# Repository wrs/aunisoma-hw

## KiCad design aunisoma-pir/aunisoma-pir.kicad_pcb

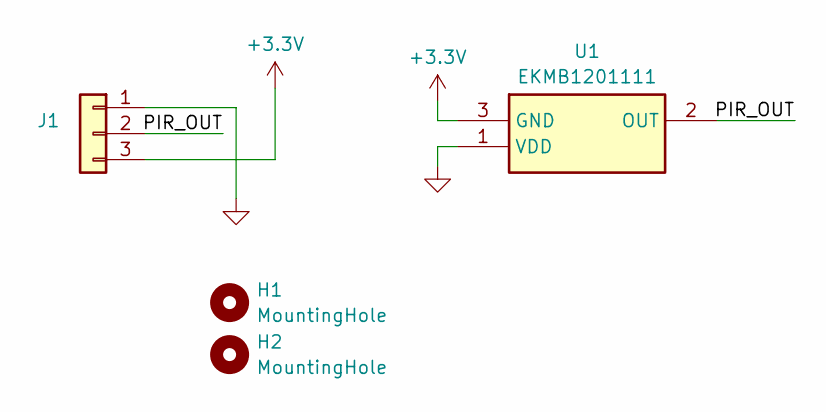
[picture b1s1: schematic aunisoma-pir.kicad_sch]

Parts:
H1, H2: MountingHole; MountingHole_3.2mm_M3
J1: PIR1; JST_PH_B3B-PH-K_1x03_P2.00mm_Vertical
U1: EKMB1201111; Mouser Part Number 769-EKMB1201111

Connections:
+3.3V: J1.3, U1.3 (GND)
/PIR_OUT: J1.2, U1.2 (OUT)
GND: J1.1, U1.1 (VDD)

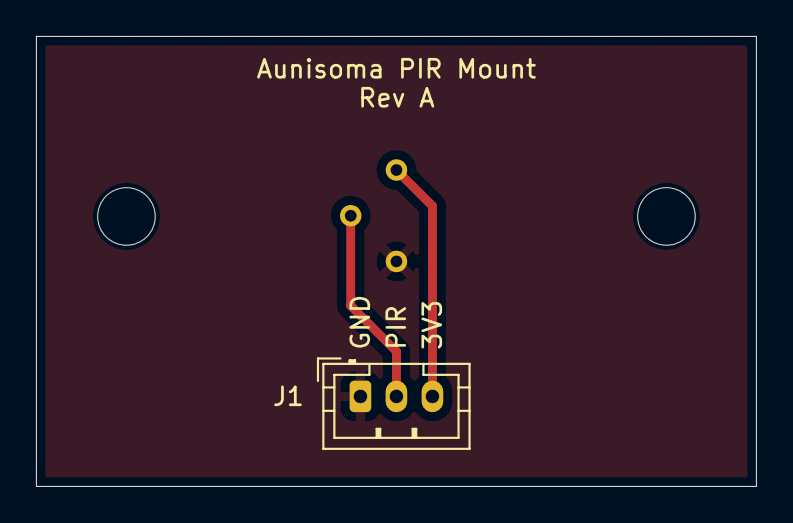
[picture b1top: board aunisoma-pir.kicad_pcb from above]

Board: 2 copper layers, 40.0 x 25.0 mm, 4 parts (1 on the bottom side), 3 nets.

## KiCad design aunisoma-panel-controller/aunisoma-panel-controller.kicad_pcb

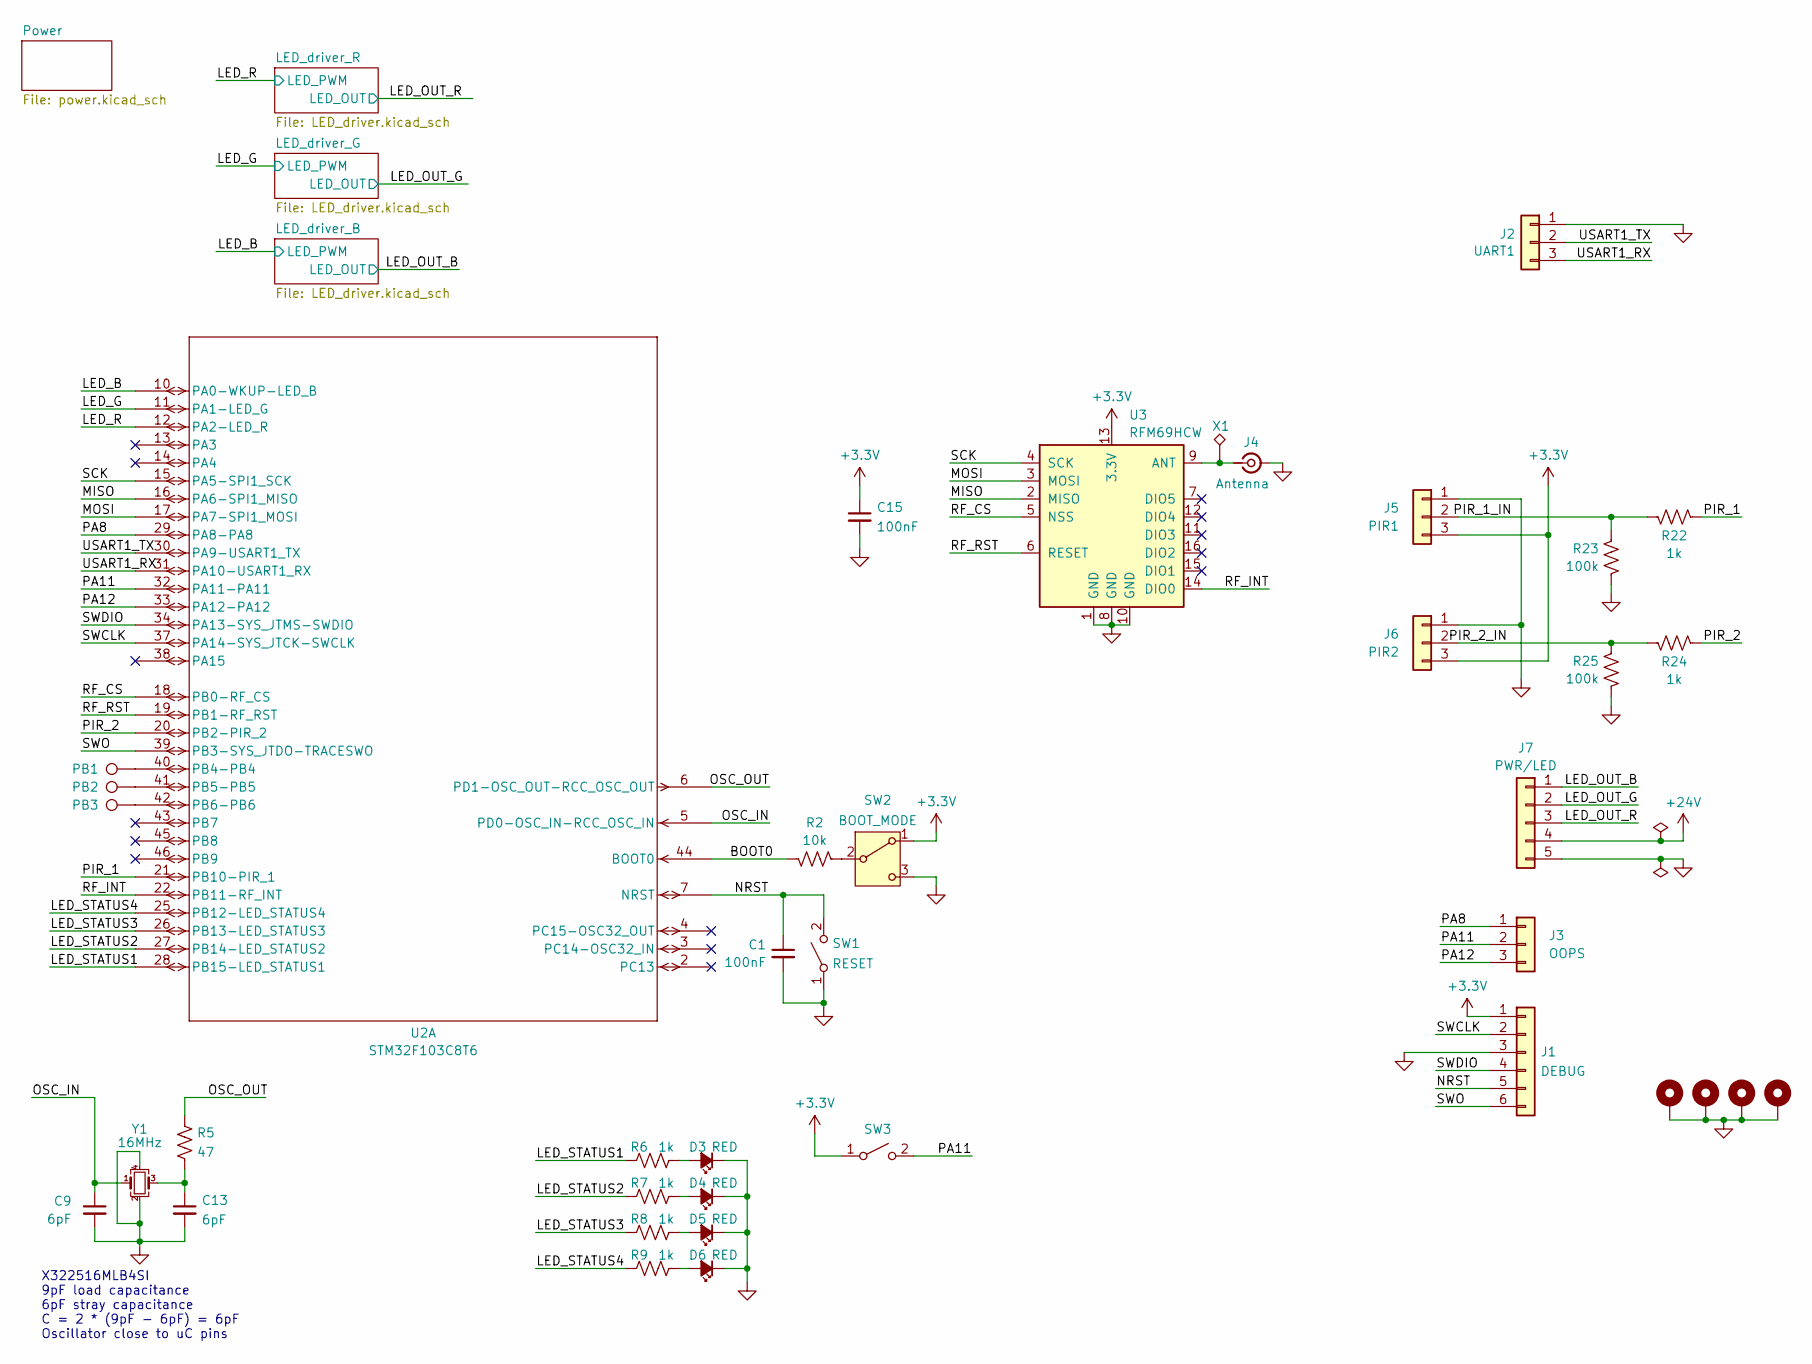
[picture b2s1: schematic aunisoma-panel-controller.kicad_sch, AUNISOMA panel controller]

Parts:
C1, C15: 100nF; C_0402_1005Metric; LCSC C1525
C9, C13: 6pF; C_0603_1608Metric; LCSC C37474
D3, D4, D5, D6: RED; LED_0805_2012Metric; LCSC C84256
H1, H2, H3, H4: MountingHole_Pad; MountingHole_3.2mm_M3_Pad_Via
J1: DEBUG; PinHeader_1x06_P2.54mm_Vertical
J2: UART1; PinHeader_1x03_P2.54mm_Vertical
J3: OOPS; PinHeader_1x03_P2.54mm_Vertical
J4: Conn_Coaxial_Small; IPEX-SMD_KMC1001-F007-7F; LCSC C426219
J5: PIR1; JST_PH_B3B-PH-K_1x03_P2.00mm_Vertical
J6: PIR2; JST_PH_B3B-PH-K_1x03_P2.00mm_Vertical
J7: PWR/LED; JST_PH_B5B-PH-K_1x05_P2.00mm_Vertical; LCSC C158028
PB1, PB2, PB3: TestPoint; TestPoint_Pad_1.0x1.0mm
R2: 10k; R_0603_1608Metric; LCSC C25804
R5: 47; R_0603_1608Metric; LCSC C23182
R6, R7, R8, R9: 1k; R_0603_1608Metric; LCSC C8218
R22, R24: 1k; R_0603_1608Metric; LCSC C25803
R23, R25: 100k; R_0603_1608Metric; LCSC C25803
SW1, SW3: SW-SMD_4P-L5.1-W5.1-P3.70-LS6.5-TL-2
SW2: SW_SPDT_PCM12; LCSC C109335
U2: STM32F103C8T6; LQFP-48_7x7mm_P0.5mm; LCSC C8734
U3: RFM69HCW; HOPERF_RFM69HW_SMD_TH
X1: Antenna; TestPoint_THTPad_D2.0mm_Drill1.0mm
Y1: 16MHz; Crystal_SMD_3225-4Pin_3.2x2.5mm; LCSC C13738

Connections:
+3.3V: C15.1, J1.1, J5.3, J6.3, SW2.1 (A), SW3.1 (A), U3.13 (3.3V); also elsewhere on the board
+24V: J7.4; also elsewhere on the board
/BOOT0: R2.2, U2.44 (BOOT0)
/LED_B: U2.10 (PA0-WKUP-LED_B); also elsewhere on the board
/LED_G: U2.11 (PA1-LED_G); also elsewhere on the board
/LED_OUT_B: J7.1; also elsewhere on the board
/LED_OUT_G: J7.2; also elsewhere on the board
/LED_OUT_R: J7.3; also elsewhere on the board
/LED_R: U2.12 (PA2-LED_R); also elsewhere on the board
/LED_STATUS1: R6.2, U2.28 (PB15-LED_STATUS1)
/LED_STATUS2: R7.2, U2.27 (PB14-LED_STATUS2)
/LED_STATUS3: R8.2, U2.26 (PB13-LED_STATUS3)
/LED_STATUS4: R9.2, U2.25 (PB12-LED_STATUS4)
/MISO: U2.16 (PA6-SPI1_MISO), U3.2 (MISO)
/MOSI: U2.17 (PA7-SPI1_MOSI), U3.3 (MOSI)
/NRST: C1.1, J1.5, SW1.2 (B), U2.7 (NRST)
/OSC_IN: C9.1, U2.5 (PD0-OSC_IN-RCC_OSC_IN), Y1.1
/OSC_OUT: R5.2, U2.6 (PD1-OSC_OUT-RCC_OSC_OUT)
/PA8: J3.1, U2.29 (PA8-PA8)
/PA11: J3.2, SW3.2 (B), U2.32 (PA11-PA11)
/PA12: J3.3, U2.33 (PA12-PA12)
/PIR_1: R22.1, U2.21 (PB10-PIR_1)
/PIR_1_IN: J5.2, R22.2, R23.2
/PIR_2: R24.1, U2.20 (PB2-PIR_2)
/PIR_2_IN: J6.2, R24.2, R25.2
/RF_CS: U2.18 (PB0-RF_CS), U3.5 (NSS)
/RF_INT: U2.22 (PB11-RF_INT), U3.14 (DIO0)
/RF_RST: U2.19 (PB1-RF_RST), U3.6 (RESET)
/SCK: U2.15 (PA5-SPI1_SCK), U3.4 (SCK)
/SWCLK: J1.2, U2.37 (PA14-SYS_JTCK-SWCLK)
/SWDIO: J1.4, U2.34 (PA13-SYS_JTMS-SWDIO)
/SWO: J1.6, U2.39 (PB3-SYS_JTDO-TRACESWO)
/USART1_RX: J2.3, U2.31 (PA10-USART1_RX)
/USART1_TX: J2.2, U2.30 (PA9-USART1_TX)
GND: C1.2, C9.2, C13.2, C15.2, D3.1 (K), D4.1 (K), D5.1 (K), D6.1 (K), H1.1, H2.1, H3.1, H4.1, J1.3, J2.1, J4.2 (Ext), J5.1, J6.1, J7.5, R23.1, R25.1, SW1.1 (A), SW2.3 (C), U3.1 (GND), U3.8 (GND), U3.10 (GND), Y1.2, Y1.4; also elsewhere on the board
unnamed: C13.1, R5.1, Y1.3
unnamed: D3.2 (A), R6.1
unnamed: D4.2 (A), R7.1
unnamed: D5.2 (A), R8.1
unnamed: D6.2 (A), R9.1
unnamed: J4.1 (In), U3.9 (ANT), X1.1
unnamed: R2.1, SW2.2 (B)
unnamed: PB1.1, U2.40 (PB4-PB4)
unnamed: PB2.1, U2.41 (PB5-PB5)
unnamed: PB3.1, U2.42 (PB6-PB6)

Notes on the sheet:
X322516MLB4SI 9pF load capacitance 6pF stray capacitance C = 2 * (9pF - 6pF) = 6pF Oscillator close to uC pins

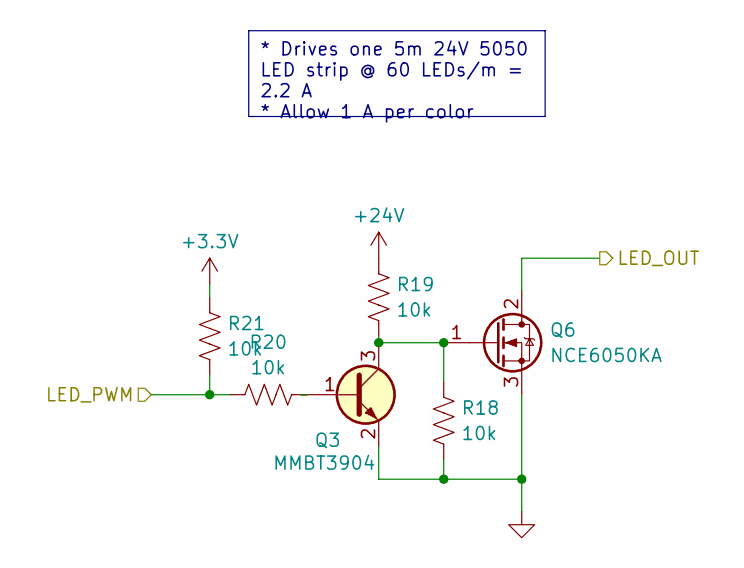
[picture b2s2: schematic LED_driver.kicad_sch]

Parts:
Q3: MMBT3904; SOT-23; LCSC C20526
Q6: NCE6050KA; TO-252-2; LCSC C620154
R18, R19, R20, R21: 10k; R_0603_1608Metric; LCSC C25803

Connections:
+3.3V: R21.2; also elsewhere on the board
+24V: R19.2; also elsewhere on the board
/LED_OUT_R: Q6.2 (D); also elsewhere on the board
/LED_R: R20.2, R21.1; also elsewhere on the board
GND: Q3.2 (E), Q6.3 (S), R18.1; also elsewhere on the board
unnamed: Q3.1 (B), R20.1
unnamed: Q3.3 (C), Q6.1 (G), R18.2, R19.1

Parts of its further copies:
Q1, Q2: MMBT3904; SOT-23; LCSC C20526
Q4, Q5: NCE6050KA; TO-252-2; LCSC C620154
R10, R11, R12, R13, R14, R15, R16, R17: 10k; R_0603_1608Metric; LCSC C25803

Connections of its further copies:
+3.3V: R13.2, R17.2; also elsewhere on the board
+24V: R11.2, R15.2; also elsewhere on the board
/LED_B: R12.2, R13.1; also elsewhere on the board
/LED_G: R16.2, R17.1; also elsewhere on the board
/LED_OUT_B: Q4.2 (D); also elsewhere on the board
/LED_OUT_G: Q5.2 (D); also elsewhere on the board
GND: Q1.2 (E), Q2.2 (E), Q4.3 (S), Q5.3 (S), R10.1, R14.1; also elsewhere on the board
unnamed: Q1.1 (B), R12.1
unnamed: Q1.3 (C), Q4.1 (G), R10.2, R11.1
unnamed: Q2.1 (B), R16.1
unnamed: Q2.3 (C), Q5.1 (G), R14.2, R15.1

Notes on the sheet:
* Drives one 5m 24V 5050 LED strip @ 60 LEDs/m = 2.2 A * Allow 1 A per color

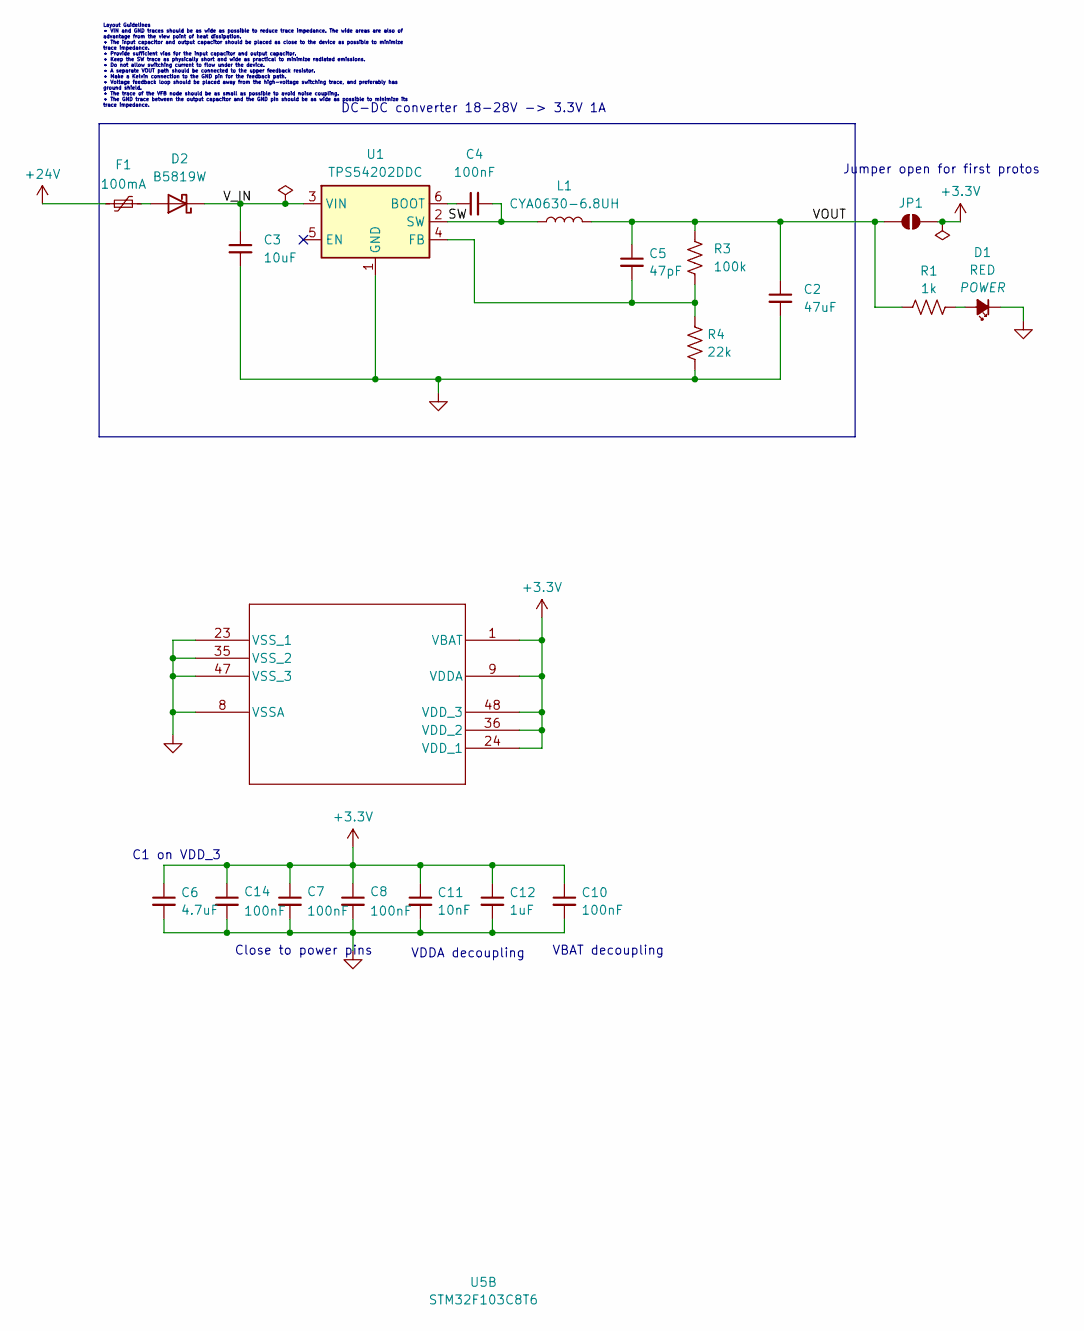
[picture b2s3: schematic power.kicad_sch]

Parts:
C2: 47uF; C_1206_3216Metric; LCSC C21122
C3: 10uF; C_0603_1608Metric; LCSC C96446
C4: 100nF; C_0603_1608Metric; LCSC C14663
C5: 47pF; C_0603_1608Metric; LCSC C96446
C6: 4.7uF; C_0603_1608Metric; LCSC C96446
C7, C8, C10, C14: 100nF; C_0402_1005Metric; LCSC C1525
C11: 10nF; C_0402_1005Metric; LCSC C1525
C12: 1uF; C_0402_1005Metric; LCSC C52923
D1: RED; LED_0805_2012Metric; LCSC C84256
D2: B5819W; D_SOD-123; LCSC C8598
F1: 100mA; Fuse_1812_4532Metric; LCSC C2760281
JP1: SolderJumper_2_Bridged; SolderJumper-2_P1.3mm_Open_RoundedPad1.0x1.5mm
L1: CYA0630-6.8UH; IND-SMD_L7.2-W6.6_GPSR0730; LCSC C5189749
R1: 1k; R_0603_1608Metric; LCSC C8218
R3: 100k; R_0603_1608Metric; LCSC C22790
R4: 22k; R_0603_1608Metric; LCSC C23018
U1: TPS54202DDC; SOT-23-6; LCSC C191884
U5: STM32F103C8T6; LQFP-48_7x7mm_P0.5mm; LCSC C8734

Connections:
+3.3V: C6.1, C7.1, C8.1, C10.1, C11.1, C12.1, C14.1, JP1.2 (B); also elsewhere on the board
+24V: F1.1; also elsewhere on the board
/Power/SW: C4.2, L1.1, U1.2 (SW)
/Power/VOUT: C2.1, C5.1, JP1.1 (A), L1.2, R1.2, R3.1
/Power/V_IN: C3.1, D2.1 (K), U1.3 (VIN)
GND: C2.2, C3.2, C6.2, C7.2, C8.2, C10.2, C11.2, C12.2, C14.2, D1.1 (K), R4.2, U1.1 (GND); also elsewhere on the board
unnamed: D1.2 (A), R1.1
unnamed: D2.2 (A), F1.2
unnamed: C4.1, U1.6 (BOOT)
unnamed: C5.2, R3.2, R4.1, U1.4 (FB)

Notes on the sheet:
DC-DC converter 18-28V -> 3.3V 1A
Jumper open for first protos
VDDA decoupling
Layout Guidelines • VIN and GND traces should be as wide as possible to reduce trace impedance. The wide areas are also of advantage from the view point of heat dissipation. • The input capacitor and output capacitor should be placed as close to the device as possible to minimize trace impedance. •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
C1 on VDD_3
Close to power pins
VBAT decoupling

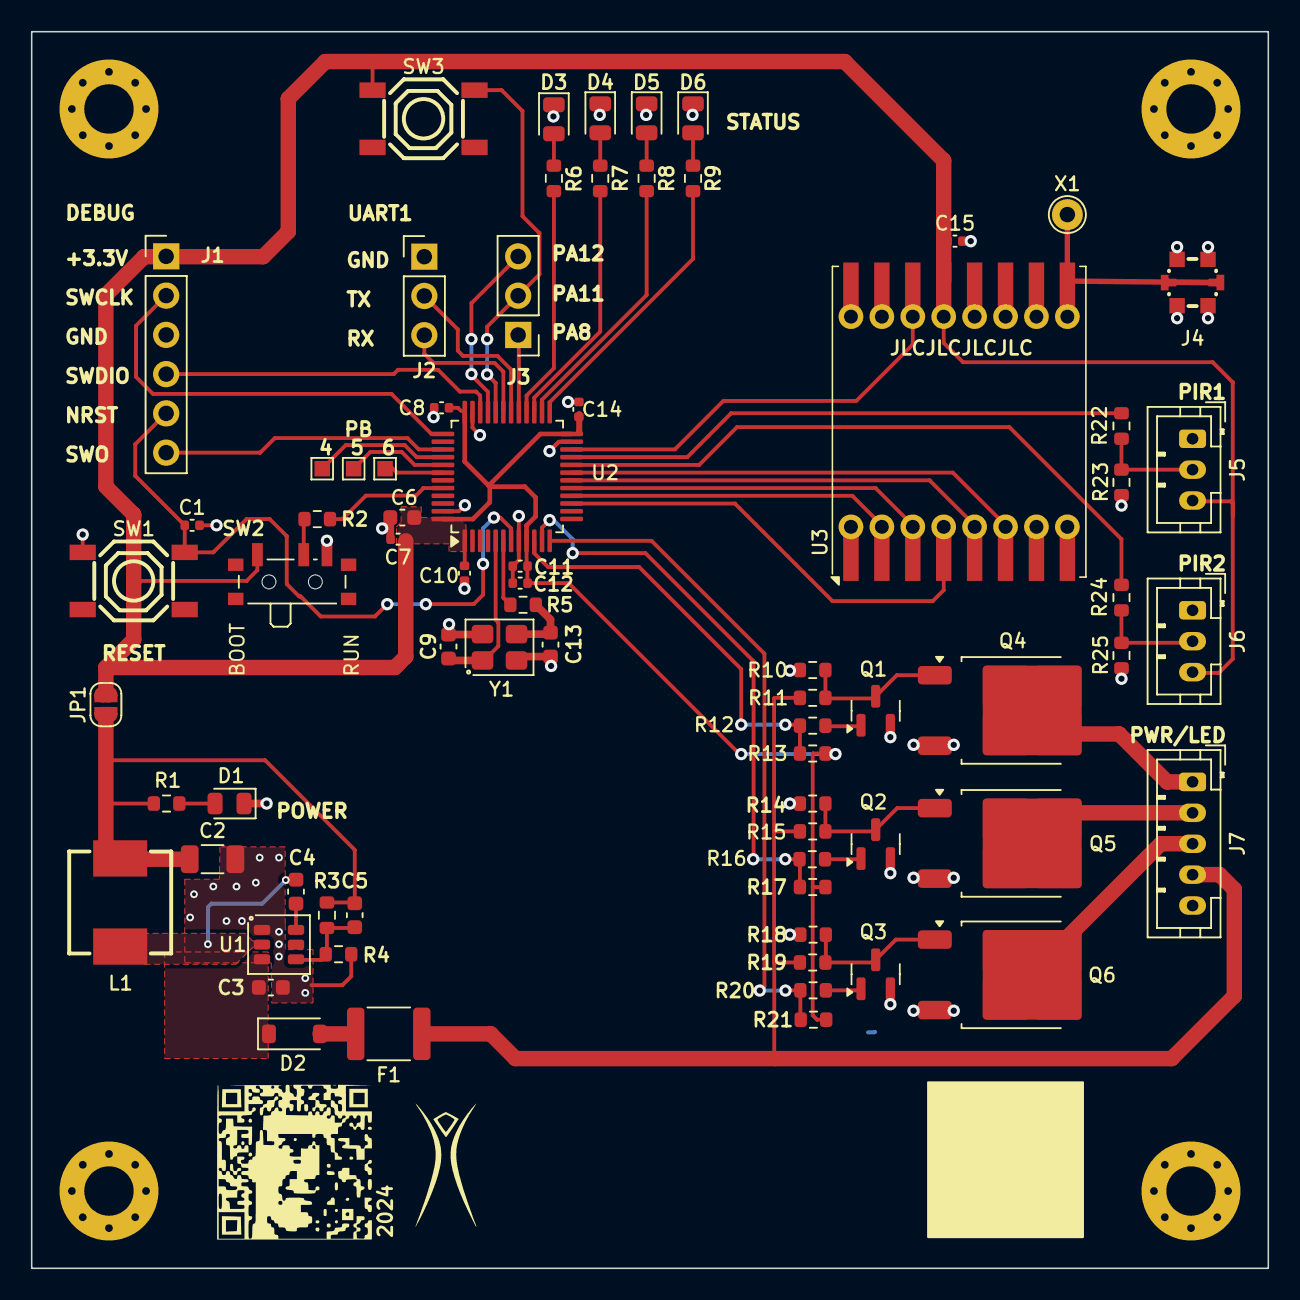
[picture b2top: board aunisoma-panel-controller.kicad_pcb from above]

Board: 2 copper layers, 80.0 x 80.0 mm, 78 parts (0 on the bottom side), 58 nets.

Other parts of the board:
LOGO: LOGO

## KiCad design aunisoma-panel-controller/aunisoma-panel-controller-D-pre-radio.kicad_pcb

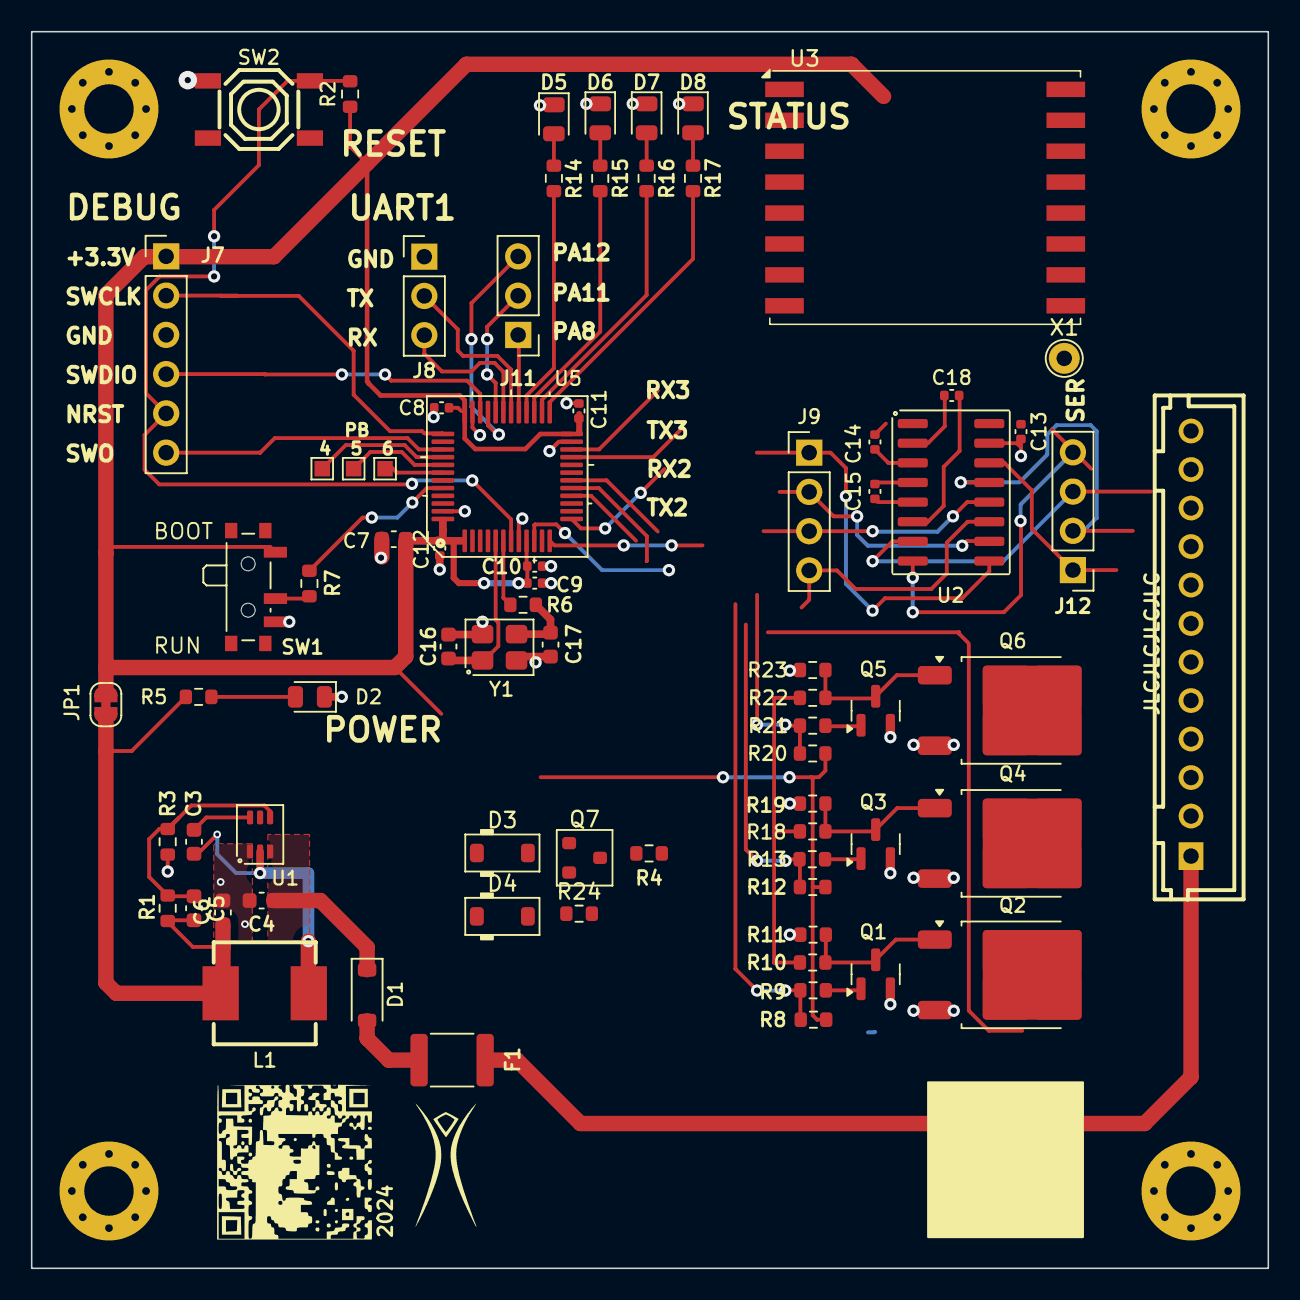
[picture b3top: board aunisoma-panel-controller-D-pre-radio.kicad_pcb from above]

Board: 2 copper layers, 80.0 x 80.0 mm, 80 parts (0 on the bottom side), 64 nets.

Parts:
C3: 100nF; C_0603_1608Metric
C4, C7: 10uF; C_0603_1608Metric
C5: 56pF; C_0603_1608Metric
C6: 47uF; C_0603_1608Metric
C8, C9, C11, C12, C13, C14, C15, C18: 100nF; C_0402_1005Metric
C10: 1uF; C_0402_1005Metric
C16, C17: 6pF; C_0603_1608Metric
D1: B5819W; D_SOD-123
D2, D5, D6, D7, D8: RED; LED_0805_2012Metric
D3, D4: 1N4148; D_SOD-123
F1: 100mA; Fuse_1812_4532Metric
H1, H2, H3, H4: MountingHole_Pad; MountingHole_3.2mm_M3_Pad_Via
J3: PWR/PERIPH; CONN-TH_B12B-XH-A-LF-SN
J7: DEBUG; PinHeader_1x06_P2.54mm_Vertical
J8: UART1; PinHeader_1x03_P2.54mm_Vertical
J9: TEST; PinHeader_1x04_P2.54mm_Vertical
J11: OOPS; PinHeader_1x03_P2.54mm_Vertical
J12: SER23; PinHeader_1x04_P2.54mm_Vertical
JP1: SolderJumper_2_Bridged; SolderJumper-2_P1.3mm_Bridged_RoundedPad1.0x1.5mm
L1: CYA0630-6.8UH; IND-SMD_L7.2-W6.6_GPSR0730
LOGO: LOGO
PB4, PB5, PB6: TestPoint; TestPoint_Pad_1.0x1.0mm
Q1, Q3, Q5: MMBT3904; SOT-23
Q2, Q4, Q6: NCE6050KA; TO-252-2
Q7: 2N7002AQ; SOT-23
R1, R24: 100k; R_0603_1608Metric
R2, R4, R7, R8, R9, R10, R11, R12, R13, R18, R19, R20, R21, R22, R23: 10k; R_0603_1608Metric
R3: 22.1k; R_0603_1608Metric
R5, R14, R15, R16, R17: 1k; R_0603_1608Metric
R6: 47; R_0603_1608Metric
SW1: SW_SPDT_PCM12
SW2: SW-SMD_4P-L5.1-W5.1-P3.70-LS6.5-TL-2
U1: TPS54202DDC; Texas_R-PDSO-G6
U2: SP3232EU; SOIC-16_3.9x9.9mm_P1.27mm
U3: RFM69HCW; HOPERF_RFM69HW
U5: STM32F103C8T6; LQFP-48_7x7mm_P0.5mm
X1: Antenna; TestPoint_THTPad_D2.0mm_Drill1.0mm
Y1: 16MHz; Crystal_SMD_3225-4Pin_3.2x2.5mm

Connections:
+3.3V: C7.1, C8.1, C9.1, C10.1, C11.1, C12.1, C13.1, J7.1, JP1.2 (B), R2.1, R4.1, R8.2, R12.2, R20.2, SW1.1 (A), U2.16 (VCC), U3.13 (3.3V), U5.1 (VBAT), U5.9 (VDDA), U5.24 (VDD), U5.36 (VDD), U5.48 (VDD)
+24V: F1.1, J3.1, R10.2, R18.2, R22.2
/BOOT0: R7.2, U5.44 (BOOT0)
/LED_B: R20.1, R21.2, U5.18 (PB0)
/LED_G: R12.1, R13.2, U5.17 (PA7)
/LED_OUT_B: J3.7, Q6.2 (D)
/LED_OUT_G: J3.6, Q4.2 (D)
/LED_OUT_R: J3.5, Q2.2 (D)
/LED_R: R8.1, R9.2, U5.16 (PA6)
/LED_STATUS1: R14.2, U5.28 (PB15)
/LED_STATUS2: R15.2, U5.27 (PB14)
/LED_STATUS3: R16.2, U5.26 (PB13)
/LED_STATUS4: R17.2, U5.25 (PB12)
/OSC_IN: C16.1, U5.5 (PD0), Y1.1
/OSC_OUT: R6.2, U5.6 (PD1)
/PIR_IN: Q7.3 (D), R4.2
/Power/VOUT: C5.1, C6.1, JP1.1 (A), L1.2, R1.1, R5.2
/SER2_RX: J3.9, J12.2, U2.13 (R1IN)
/SER2_TX: J3.8, J12.1, U2.14 (T1OUT)
/SER3_RX: J3.11, J12.4, U2.8 (R2IN)
/SER3_TX: J3.10, J12.3, U2.7 (T2OUT)
/USART1_RX: J8.3, U5.31 (PA10)
/USART1_TX: J8.2, U5.30 (PA9)
/USART2_RX: J9.3, U2.12 (R1OUT), U5.13 (PA3)
/USART2_TX: J9.4, U2.11 (T1IN), U5.12 (PA2)
/USART3_RX: J9.1, U2.9 (R2OUT), U5.22 (PB11)
/USART3_TX: J9.2, U2.10 (T2IN), U5.21 (PB10)
GND: C4.2, C6.2, C7.2, C8.2, C9.2, C10.2, C11.2, C12.2, C13.2, C16.2, C17.2, D2.1 (K), D5.1 (K), D6.1 (K), D7.1 (K), D8.1 (K), H1.1, H2.1, H3.1, H4.1, J3.12, J7.3, J8.1, Q1.2 (E), Q2.3 (S), Q3.2 (E), Q4.3 (S), Q5.2 (E), Q6.3 (S), Q7.2 (S), R3.2, R11.1, R19.1, R23.1, R24.1, SW1.3 (C), SW2.1 (A), U1.1 (GND), U2.15 (GND), U3.1 (GND), U3.8 (GND), U3.10 (GND), U5.8 (VSSA), U5.23 (VSS), U5.35 (VSS), U5.47 (VSS), Y1.2, Y1.4
NRST: J7.5, R2.2, SW2.2 (B), U5.7 (NRST)
unnamed: C17.1, R6.1, Y1.3
unnamed: D1.2 (A), F1.2
unnamed: C4.1, D1.1 (K), U1.3 (VIN)
unnamed: D2.2 (A), R5.1
unnamed: D3.1 (K), D4.1 (K), Q7.1 (G), R24.2
unnamed: D5.2 (A), R14.1
unnamed: D6.2 (A), R15.1
unnamed: D7.2 (A), R16.1
unnamed: D8.2 (A), R17.1
unnamed: Q1.1 (B), R9.1
unnamed: Q1.3 (C), Q2.1 (G), R10.1, R11.2
unnamed: Q3.1 (B), R13.1
unnamed: Q3.3 (C), Q4.1 (G), R18.1, R19.2
unnamed: Q5.1 (B), R21.1
unnamed: Q5.3 (C), Q6.1 (G), R22.1, R23.2
unnamed: R7.1, SW1.2 (B)
unnamed: C3.1, U1.6 (BOOT)
unnamed: C5.2, R1.2, R3.1, U1.4 (FB)
unnamed: C3.2, L1.1, U1.2 (SW)
unnamed: C14.1, U2.1 (C1+)
unnamed: C14.2, U2.3 (C1-)
unnamed: C15.1, U2.4 (C2+)
unnamed: C15.2, U2.5 (C2-)
unnamed: C18.1, U2.2 (V+)
unnamed: C18.2, U2.6 (V-)
unnamed: U3.9 (ANT), X1.1
PA8: J11.1, U5.29 (PA8)
PA11: J11.2, U5.32 (PA11)
PA12: J11.3, U5.33 (PA12)
PB4: PB4.1, U5.40 (PB4)
PB5: PB5.1, U5.41 (PB5)
PB6: PB6.1, U5.42 (PB6)
SWCLK: J7.2, U5.37 (PA14)
SWDIO: J7.4, U5.34 (PA13)
SWO: J7.6, U5.39 (PB3)

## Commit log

2024-08-31 Initial commit after apocalypse
2024-08-31 REV D board submitted
